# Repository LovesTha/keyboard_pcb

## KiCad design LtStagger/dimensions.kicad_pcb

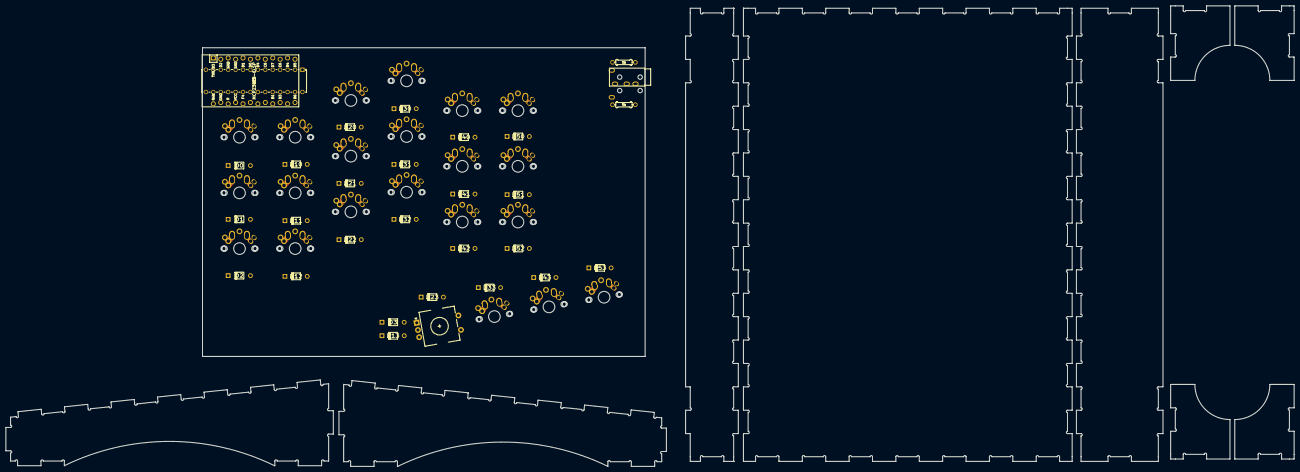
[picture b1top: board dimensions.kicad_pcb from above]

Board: 2 copper layers, 440.7 x 157.5 mm, 51 parts (1 on the bottom side), 38 nets, no tracks yet.

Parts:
D0, D1, D2: D; Diode
D3: D03; Diode
D10: D10; Diode
D11: D11; Diode
D12: D12; Diode
D13: D13; Diode
D20: D20; Diode
D21: D21; Diode
D22: D22; Diode
D23: D23; Diode
D30: D30; Diode
D31: D31; Diode
D32: D32; Diode
D33: D33; Diode
D40: D40; Diode
D41: D41; Diode
D42: D42; Diode
D43: D43; Diode
D50: D50; Diode
D51: D51; Diode
D52: D52; Diode
D53: D53; Diode
K0: K00; Triple-Dual-1u
K1: K01; Triple-Dual-1u
K2: K02; Triple-Dual-1u
K10: K10; Triple-Dual-1u
K11: K11; Triple-Dual-1u
K12: K12; Triple-Dual-1u
K20: K20; Triple-Dual-1u
K21: K21; Triple-Dual-1u
K22: K22; Triple-Dual-1u
K30: K30; Triple-Dual-1u
K31: K31; Triple-Dual-1u
K32: K32; Triple-Dual-1u
K33: K33; Triple-Dual-1u
K40: K40; Triple-Dual-1u
K41: K41; Triple-Dual-1u
K42: K42; Triple-Dual-1u
K43: K43; Triple-Dual-1u
K50: K50; Triple-Dual-1u
K51: K51; Triple-Dual-1u
K53: K53; Triple-Dual-1u
L52: K52; Triple-Dual-1u
R4, R5: 5k; Resistor-Compact
SW1: Rotary_Encoder_Switch; RotaryEncoder_EC11
U1: ProMicro; ArduinoProMicro-ZigZag
U2: TRRS; TRRS-PJ-320A-dual
U3: MCP23018-E_SP; MCP23018

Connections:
Col0: D3.2, K0.1, K1.1, K2.1, U1.18, U3.21
Col1: D13.2, K10.1, K11.1, K12.1, U1.17, U3.22
Col2: K20.1, K21.1, K22.1, SW1.S1, U1.16, U3.23
Col3: K30.1, K31.1, K32.1, K33.1, U1.15, U3.24
Col4: K40.1, K41.1, K42.1, K43.1, U1.14, U3.25
Col5: K50.1, K51.1, K53.1, L52.1, U1.13, U3.26
GND: U1.3, U1.4, U1.23, U2.2, U3.1
unnamed: D0.2, K0.2
unnamed: D1.2, K1.2
unnamed: D2.2, K2.2
unnamed: D3.1, SW1.A
unnamed: D10.2, K10.2
unnamed: D11.2, K11.2
unnamed: D12.2, K12.2
unnamed: D13.1, SW1.B
unnamed: D20.2, K20.2
unnamed: D21.2, K21.2
unnamed: D22.2, K22.2
unnamed: D23.2, SW1.S2
unnamed: D30.2, K30.2
unnamed: D31.2, K31.2
unnamed: D32.2, K32.2
unnamed: D33.2, K33.2
unnamed: D40.2, K40.2
unnamed: D41.2, K41.2
unnamed: D42.2, K42.2
unnamed: D43.2, K43.2
unnamed: D50.2, K50.2
unnamed: D51.2, K51.2
unnamed: D52.2, L52.2
unnamed: D53.2, K53.2
Row0: D0.1, D10.1, D20.1, D30.1, D40.1, D50.1, U1.7, U3.6
Row1: D1.1, D11.1, D21.1, D31.1, D41.1, D51.1, U1.8, U3.5
Row2: D2.1, D12.1, D22.1, D32.1, D42.1, D52.1, U1.9, U3.4
Row3: D23.1, D33.1, D43.1, D53.1, SW1.C, U1.10, U3.3
SCL: R5.2, U1.5, U2.3
SDA: R4.2, U1.6, U2.4
VCC: R4.1, R5.1, U1.21, U2.1, U3.11

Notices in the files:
parts and their libraries:
Copyright 2016 Accelerated Designs. All rights reserved.
